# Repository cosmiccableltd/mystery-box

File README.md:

# Mystery Box

## About
The Mystery Box is a small PCB which provides power ports for various devices to indicate a ringing phone and drive POE devices.
It was designed by [Cosmic Cable Ltd.](http://cosmic.cable.limited) to be used for self-made telephone booths. 

## Ports
| Port Name | Function                                                      | Usage                                   |
| --------- | --------                                                      | -----                                   |
| J1        | [POE](https://en.wikipedia.org/wiki/Power_over_Ethernet) Port | POE powered network device              |
| J2        | LAN Port                                                      | Connection to external network          |
| J3        | Analogue Telephone Port                                       | Connection to external analogue network |
| J4        | Analogue Telephone Port                                       | Connection to analogue telephone        |
| X1-1      | +12V                                                          |                                         |
| X1-2      |  GND (switched)                                               | swichted on ringing phone line          |
| X1-3      | +12V                                                          |                                         |
| X1-4      |  GND                                                          |                                         |
| X1-5      | +12V                                                          |                                         |
| X1-6      |  GND                                                          |                                         |
| X1-7      | +12V                                                          |                                         |
| X1-8      |  GND                                                          |                                         |

## Known Issues
We experienced that the PMV20EN Q2 Mosfet might die from to high current.
It should be changed to something which can handle more current or otherwise it must be ensured that the outgoing power is limited.

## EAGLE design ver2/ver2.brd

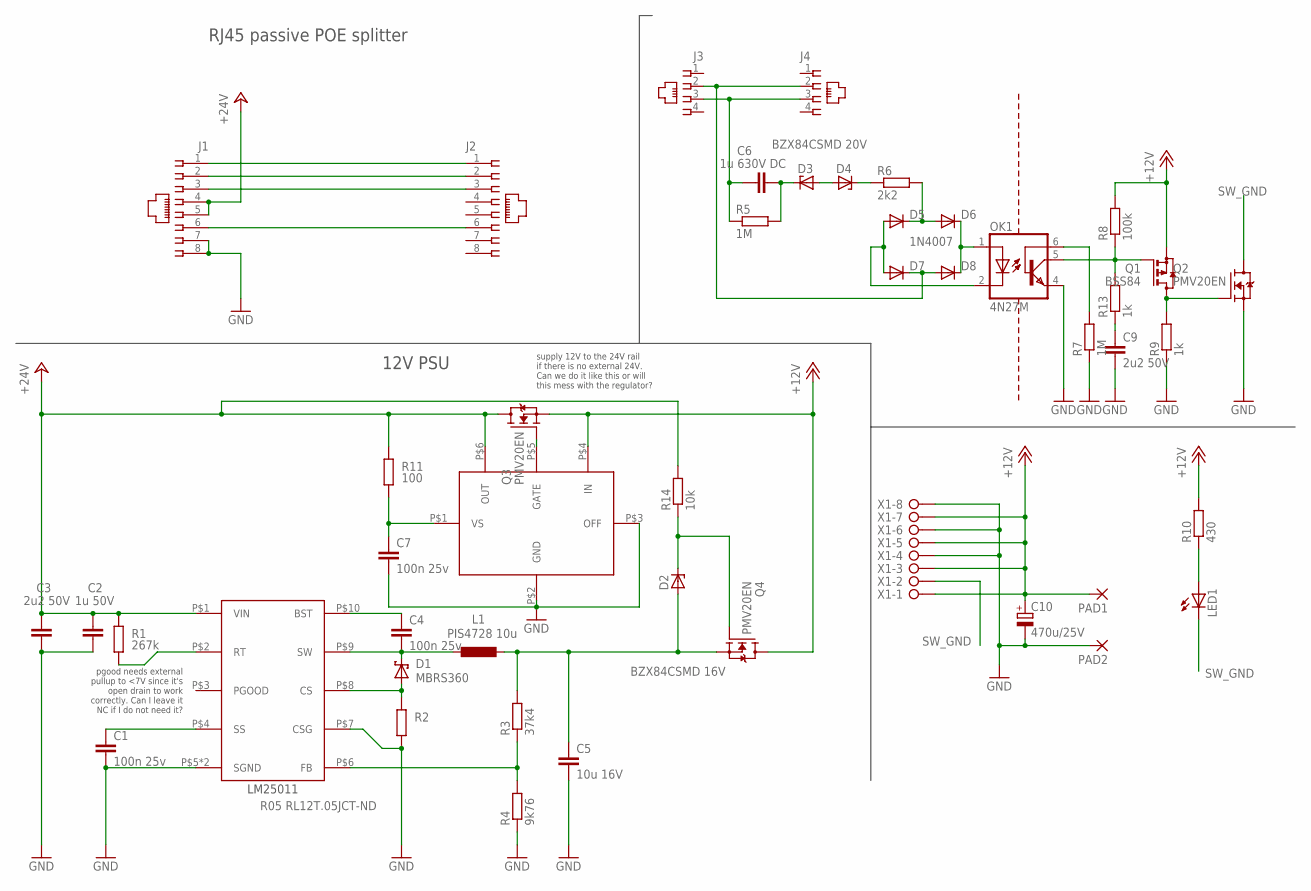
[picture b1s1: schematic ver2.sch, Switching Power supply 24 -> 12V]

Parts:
C1, C4, C7: 100n 25v; C0805K
C2: 1u 50V; C0805K
C3, C9: 2u2 50V; C1206K
C5: 10u 16V; C0805K
C6: 1u 630V DC; C275-205X316
C10: 470u/25V; E3,5-8
D1: MBRS360; SMC
D2: BZX84CSMD 16V; TO236
D3: BZX84CSMD; TO236
D4: BZX84CSMD 20V; TO236
D5, D6, D7: 1N4004; DO41-10
D8: 1N4007; DO41-10
J1, J2: 215877-4
J3, J4: 215876-6
L1: PIS4728 10u; PIS4728
LED1: LED5MM
OK1: 4N27M; DIL06
PAD1, PAD2: 3,17/1,3
Q1: BSS84; SOT23
Q2, Q3, Q4: PMV20EN; SOT23
R1: 267k; R0603
R2: R05 RL12T.05JCT-ND; R0805
R3: 37k4; R0603
R4: 9k76; R0603
R5, R7: 1M; R0805
R6: 2k2; R1206
R8: 100k; R0805
R9: 1k; R1206
R10: 430; R1206
R11: 100; R0603
R13: 1k; R0805
R14: 10k; R0805
U$1: LM25011; HVSSOP-10
U$2: LM5050; SOT-23-6
X1: AKL382-8; ALK382-8

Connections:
+12V: C10.+, PAD1.1, Q1.2 (S), Q3.2 (S), Q4.3 (D), R8.2, R10.2, U$2.P$4 (IN), X1.P$1, X1.P$3, X1.P$5, X1.P$7
+24V: C2.1, C3.1, J1.4, J1.5, Q3.3 (D), R1.2, R11.2, R14.2, U$1.P$1 (VIN), U$2.P$6 (OUT)
EHT1_N: J1.2, J2.2
EHT1_P: J1.1, J2.1
ETH2_N: J1.6, J2.6
ETH2_P: J1.3, J2.3
GND: C1.2, C2.2, C3.2, C5.2, C7.2, C9.2, C10.-, J1.7, J1.8, OK1.4 (EMI), PAD2.1, Q2.2 (S), R2.1, R4.1, R7.1, R9.1, U$1.P$5 (SGND), U$1.P$7 (CSG), U$1.P$11 (SGND), U$2.P$2 (GND), U$2.P$3 (OFF), X1.P$4, X1.P$6, X1.P$8
unnamed: C1.1, U$1.P$4 (SS)
unnamed: D1.A, R2.2, U$1.P$8 (CS)
unnamed: R1.1, U$1.P$2 (RT)
unnamed: D7.C, D8.A, J3.2, J4.2
unnamed: C4.2, D1.C, L1.P$1 (1), U$1.P$9 (SW)
unnamed: C4.1, U$1.P$10 (BST)
unnamed: R3.1, R4.2, U$1.P$6 (FB)
unnamed: C6.1, J3.3, J4.3, R5.1
unnamed: C6.2, D3.C, R5.2
unnamed: D3.A, D4.A
unnamed: D4.C, R6.1
unnamed: D5.C, D6.A, R6.2
unnamed: D5.A, D7.A, OK1.2 (C)
unnamed: D6.C, D8.C, OK1.1 (A)
unnamed: Q1.3 (D), Q2.1 (G), R9.2
unnamed: OK1.6 (BAS), R7.2
unnamed: LED1.A, R10.1
unnamed: C7.1, R11.1, U$2.P$1 (VS)
unnamed: Q3.1 (G), U$2.P$5 (GATE)
unnamed: C5.1, D2.A, L1.P$2 (2), Q4.2 (S), R3.2
unnamed: D2.C, Q4.1 (G), R14.1
unnamed: C9.1, R13.1
OK_OUT: OK1.5 (COL), Q1.1 (G), R8.1, R13.2
SW_GND: LED1.K (C), Q2.3 (D), X1.P$2

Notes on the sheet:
pgood needs external pullup to <7V since it's open drain to work correctly. Can I leave it NC if I do not need it?
supply 12V to the 24V rail if there is no external 24V. Can we do it like this or will this mess with the regulator?
12V PSU
RJ45 passive POE splitter
LM25011

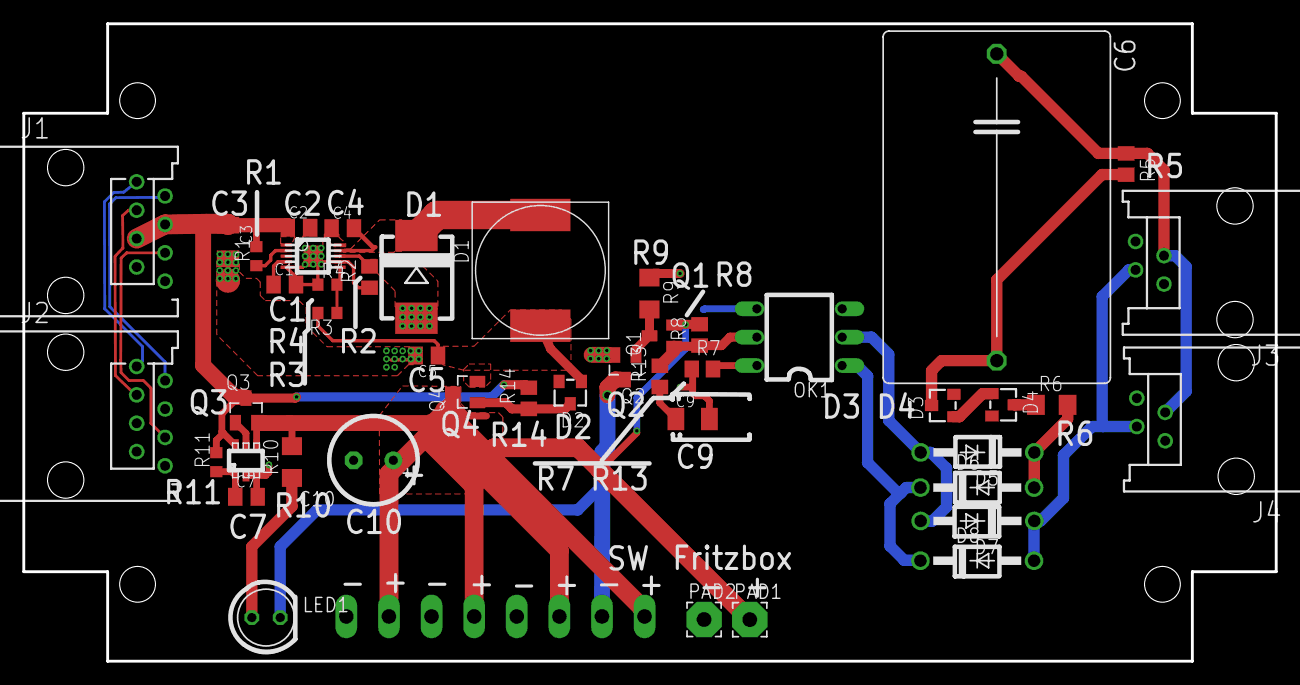
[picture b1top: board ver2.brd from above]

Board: 2 copper layers, 112.0 x 57.0 mm, 46 parts (1 on the bottom side), 31 nets.

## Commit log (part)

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2022-08-31 initial release
2022-09-01 added ver1
2022-09-01 added ver2
2022-09-01 added overview.png
2023-03-05 added ver2 pictures
2025-02-25 added first draft v3
2025-02-25 first draft v3
2025-03-05 update 2. meeting
2025-03-27 Added current PDF
2025-03-27 removed test pdf
2025-03-27 added pipeline for PDF creation
2025-04-15 added footprints for rj45, max485 module
2025-04-15 kikad symbol and footprint libraries
2025-05-06 pcb editor beginning
2025-05-07 added pcd to pdf pipeline
2025-05-07 enabled pipeline for pcb
2025-05-20 smart switch
2025-05-27 final prototype v3
2025-05-29 added notes
2025-11-05 first edit of serious ver3
2025-11-18 schematic with converter + footprints
2025-11-25 renamed ver3-prototype
2025-11-25 beginning ver3 PCB
2025-12-02 ver3: first PCB layout
2025-12-02 readded DMX
2026-01-13 beginning ver3 PCB routing
2026-02-04 v3: first draft finished
2026-02-04 ver3: all layers visible
2026-02-10 logo + silk stuff
2026-02-17 ver3: added GND to serial1
2026-02-17 ver3: gitignore zip backups
2026-02-17 ver3: RJ45 data routing on same side
2026-02-18 ver3: silkscreen beaty & 12v fused LED
2026-02-25 updated BOM
2026-02-25 ver3: fab outputs
2026-02-25 removed old stuff
2026-02-25 added BOM
2026-02-25 fixed SmartSwitch Pad
2026-02-25 mounting holes rework
2026-04-02 ver3: found some bauteile
2026-05-10 leftover changes
2026-05-10 added file
